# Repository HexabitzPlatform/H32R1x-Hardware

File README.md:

# H32R1x-Hardware
Hexabitz 3.3V to 5V/1A DC-DC Boost Module Hardware Design

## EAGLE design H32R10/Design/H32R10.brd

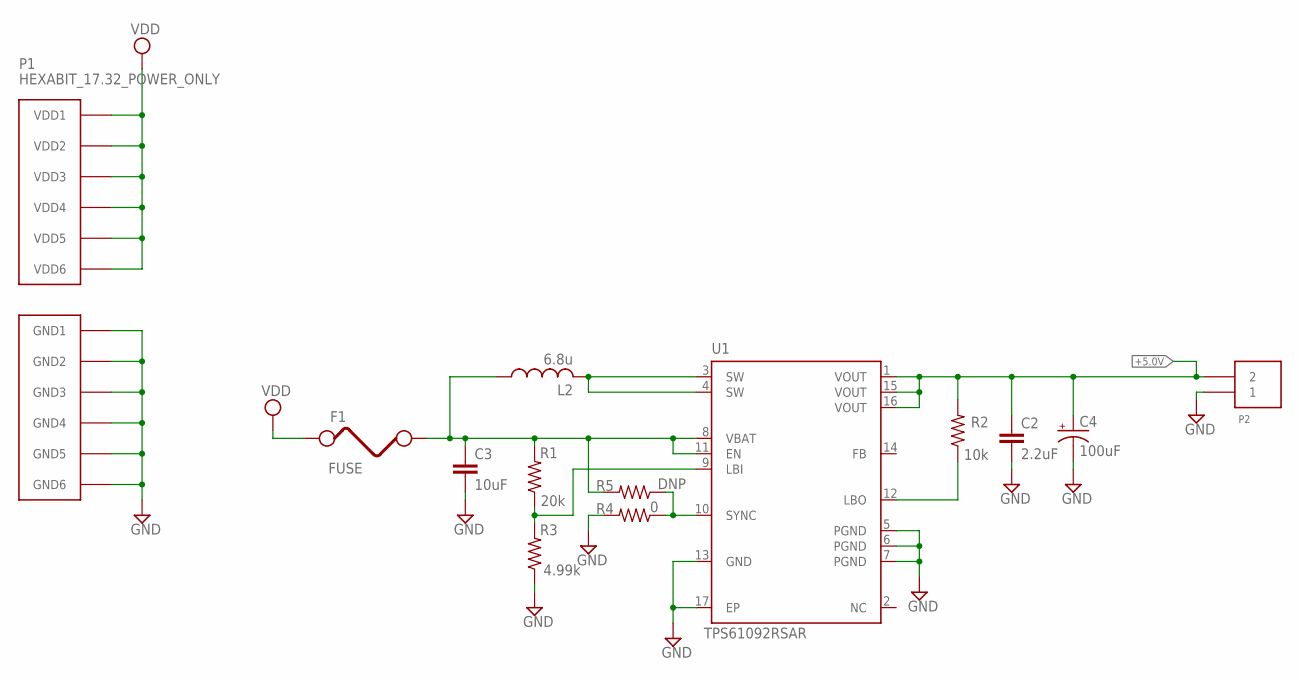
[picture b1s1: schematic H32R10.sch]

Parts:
C2: 2.2uF; C-0603; TOLERANCE ±10%; VOLTAGE_RATING 16V; MPN C1608X5R1C225K080AB
C3: 10uF; C-0603; TOLERANCE ±20%; VOLTAGE_RATING 6.3V; MPN GRM188R60J106ME84D
C4: 100uF; C-1210-POL; MPN LMK325ABJ107MMHT
F1: FUSE
L2: 6.8u; IND-7447789006
P1: HEXABIT_17.32_POWER_ONLY
P2: 691311500102
R1: 20k; R-0402; TOLERANCE 1%; MPN RC0402FR-0720KL
R2: 10k; R-0402; TOLERANCE 1%; MPN AT0402FRE0710KL
R3: 4.99k; R-0402; TOLERANCE 1%; MPN AC0402FR-074K99L
R4: 0; R-0402; MPN AC0402JR-070RL
R5: DNP; R-0402; MPN DNP
U1: TPS61092RSAR

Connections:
+5.0V: C2.1, C4.1 (+), P2.2, R2.2, U1.1 (VOUT), U1.15 (VOUT), U1.16 (VOUT)
GND: C2.2, C3.2, C4.2 (-), P1.PAD_PD7 (GND1), P1.PAD_PD8 (GND2), P1.PAD_PD9 (GND3), P1.PAD_PD10 (GND4), P1.PAD_PD11 (GND5), P1.PAD_PD12 (GND6), P2.1, R3.1, R4.2, U1.5 (PGND), U1.6 (PGND), U1.7 (PGND), U1.13 (GND), U1.17 (EP)
unnamed: R1.1, R3.2, U1.9 (LBI)
unnamed: C3.1, F1.2, L2.1, R1.2, R5.2, U1.8 (VBAT), U1.11 (EN)
unnamed: L2.2, U1.3 (SW), U1.4 (SW)
unnamed: R2.1, U1.12 (LBO)
unnamed: R4.1, R5.1, U1.10 (SYNC)
VDD: F1.1, P1.PAD_PU7 (VDD1), P1.PAD_PU8 (VDD2), P1.PAD_PU9 (VDD3), P1.PAD_PU10 (VDD4), P1.PAD_PU11 (VDD5), P1.PAD_PU12 (VDD6)

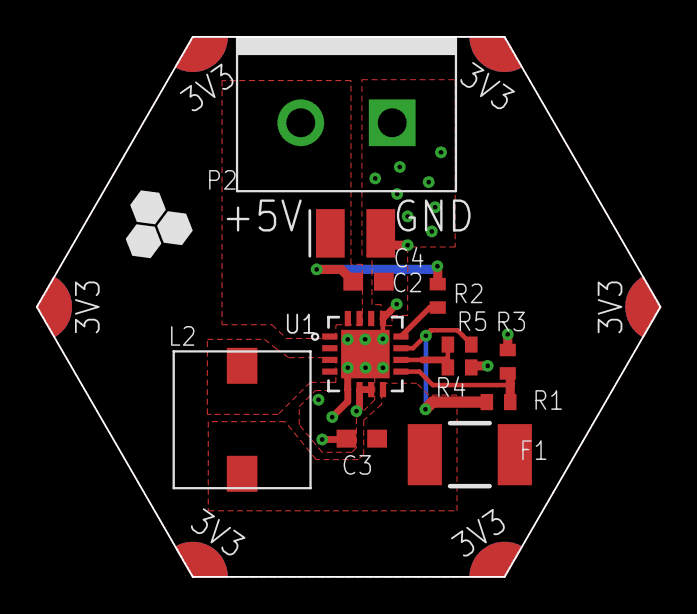
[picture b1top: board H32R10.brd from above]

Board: 2 copper layers, 34.6 x 30.0 mm, 13 parts (0 on the bottom side), 8 nets.

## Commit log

2019-05-23 First release rev 0
